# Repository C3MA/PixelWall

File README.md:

PixelWall Project

description coming soon

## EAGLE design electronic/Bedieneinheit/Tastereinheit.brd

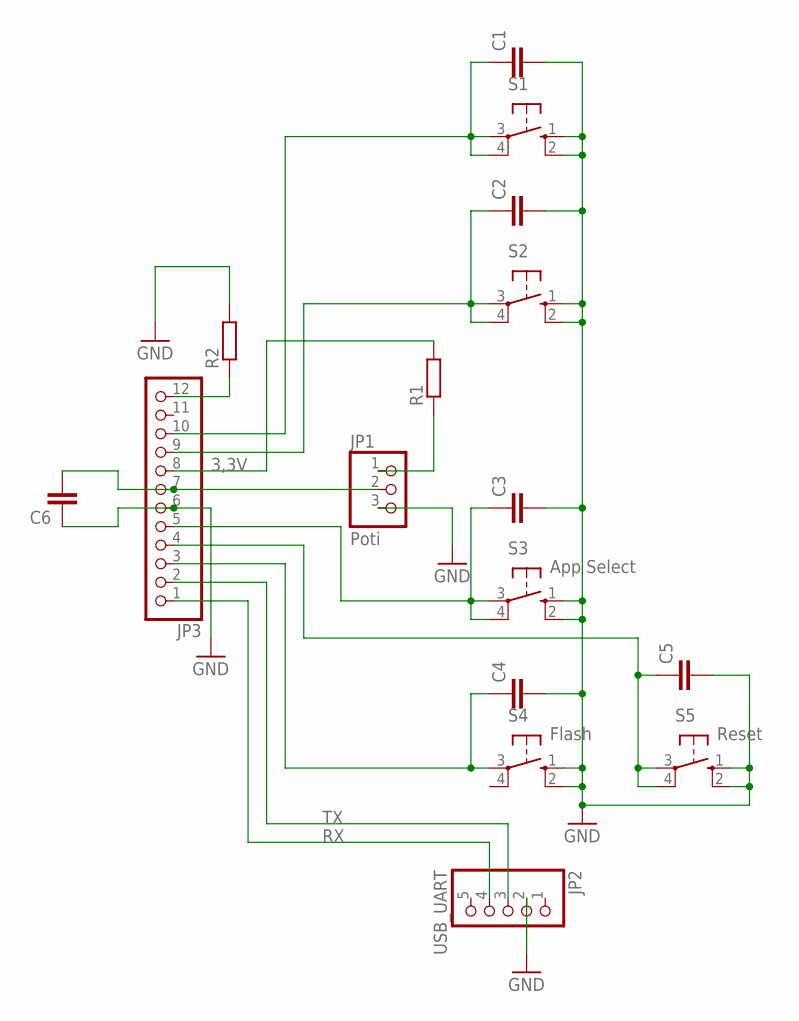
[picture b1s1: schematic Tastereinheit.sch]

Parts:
C1, C2, C3, C4, C5, C6: C-EUC0805; C0805
JP1: Poti; 1X03/90
JP2: USB_UART; 1X05/90
JP3: PINHD-1X12/90; 1X12/90
R1, R2: R-EU_R0805; R0805
S1, S2: 10-XX; B3F-10XX
S3: App Select; B3F-10XX
S4: Flash; B3F-10XX
S5: Reset; B3F-10XX

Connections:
3,3V: JP3.8, R1.2
GND: C1.2, C2.2, C3.2, C4.2, C5.2, C6.1, JP1.3, JP2.2, JP3.6, R2.2, S1.1 (S), S1.2 (S1), S2.1 (S), S2.2 (S1), S3.1 (S), S3.2 (S1), S4.1 (S), S4.2 (S1), S5.1 (S), S5.2 (S1)
unnamed: JP1.1, R1.1
unnamed: C4.1, JP3.3, S4.3
unnamed: C3.1, JP3.5, S3.3, S3.4 (P1)
unnamed: C2.1, JP3.9, S2.3, S2.4 (P1)
unnamed: C1.1, JP3.10, S1.3, S1.4 (P1)
unnamed: C6.2, JP1.2, JP3.7
unnamed: C5.1, JP3.4, S5.3, S5.4 (P1)
unnamed: JP3.12, R2.1
RX: JP2.4, JP3.1
TX: JP2.3, JP3.2

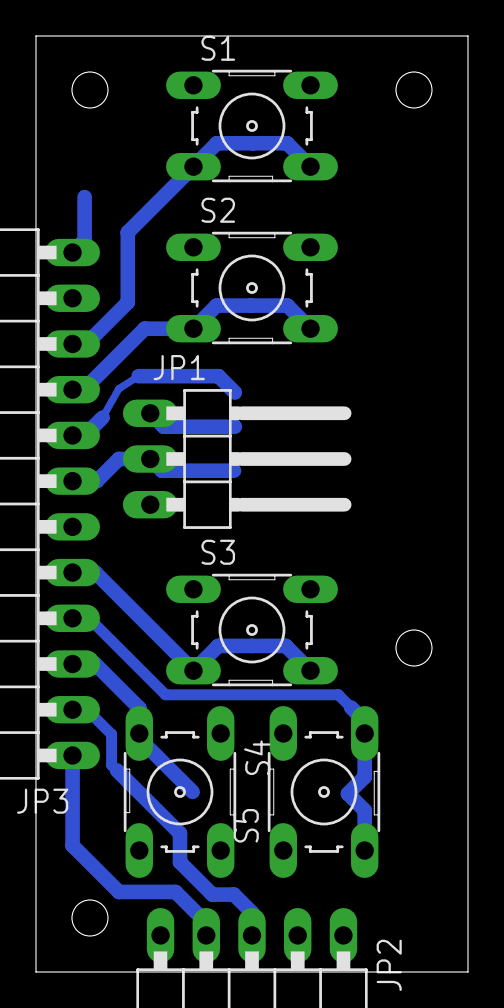
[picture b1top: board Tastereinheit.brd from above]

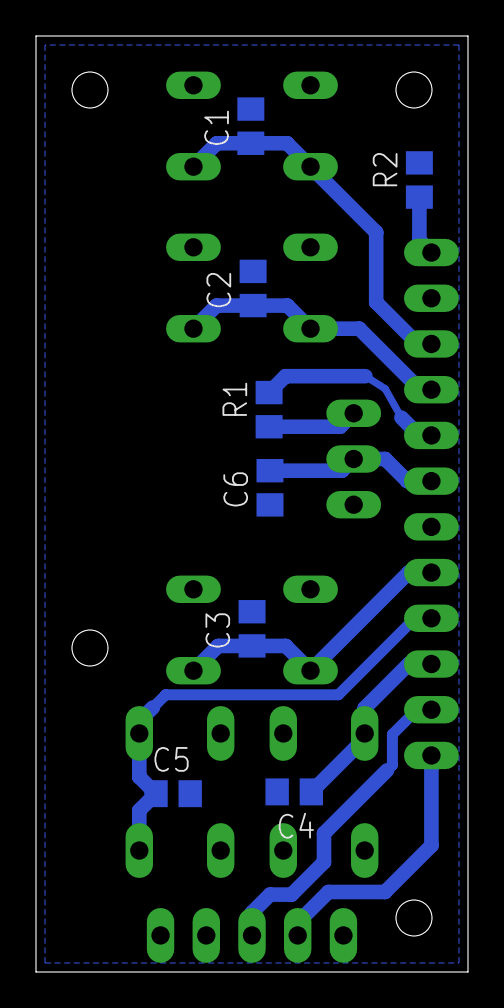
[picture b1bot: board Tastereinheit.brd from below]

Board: 2 copper layers, 24.0 x 52.0 mm, 16 parts (8 on the bottom side), 12 nets.

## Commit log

2019-04-11 first check in
2019-04-11 - snake game added - machanic parts added
2019-04-22 Bedieneinheit + NES Controller added
2019-04-23 button support added
2019-04-26 Create LICENSE
2019-04-26 Änderungen in der Bedienung GetInTouch-Anbindung aktiviert
2019-04-27 Updated with current files
2019-05-08 Averaging beim Poti einlesen hinzugefügt GetInTouch sachen auskommentiert
